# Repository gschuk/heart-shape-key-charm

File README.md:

# Heart-shape-key-charm
This project features a key charm to display simple animations using 7 SMD LEDs. The key charm is meant to be used without a case and includes a hole thoughout the PCB to connect it to a keychain.

<div>
    <div style="display:inline-block; text-align:center;">
        <br>
        <em> Front view </em>
    </div><div style="display:inline-block; text-align:center;">
        <br>
        <em> Back view </em>
    </div>
</div>

## Specification:
Microcontroller: **Attiny 84a** <br>
Powersource: **CR 2032** <br>
LEDs: **Kingsbright red (2mA)** <br>
Power Switch: **Slide Switch (EG1215AA)**<br>

## Documentation:
Software: **firmware/README.md** <br>
Hardware: **hardware/README.md** <br>

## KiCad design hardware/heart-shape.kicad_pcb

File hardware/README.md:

# Hardware
## Components (for one key charm)
- PCB: **FR-4(two layers)** [x1]
- Microcontroller: **Attiny 84a-SS** [x1]
- LEDs: **Kingsbright red (2mA)** [x7] 
- Resistor: **680 ohm (0805)** [x7] 
- Powersource: **CR2032** [x1]
- Coin Cell Holder (CR 2032): **Keystone 1060** [x1]
- Capacitor: **22uF;10V;X5R;(0805)** [x1]
- Slide Switch: **EG1215AA E-Switch** [x1]

## Schematic
<div style="display:inline-block; text-align:center;">
    <br>
    <em> Schematic </em>
</div>

## Driving LEDs
No external LED driver or amplifier was used as the low power LEDs do not require a higher output power than what the Attiny 84a already provides.
### PWM control
The Attiny 84a features 4 PWM pins. In order to control all 7 LEDs, 3 PWM pins are shared by a pair of LEDs: D1 and D4, D2 and D5 as well as D3 and D6. LED D7 does not share a PWM pin and will be driven individually. LEDs that share a PWM pin are located across each other. This allows a circular animation driving 3 neighbouring LEDs with different PWM values at the same time, as every LED and its direct 2 neighbouring LEDs are driven by individual PWM pins.
### Connection to GND or Vcc
Instead of connecting each LED to Vcc or GND statically and controlling the LEDs solely by PWM additional digital pins are used to either turn a single LED on or off. Each LED is connected to one digital pin either driving the output LOW or HIGH. For example: LED D1 and LED D4 share the same PWM signal. If these two LEDs would be statically connected to Vcc or GND they would light up identically. The additional control over the digital pins allows for LED D4 to light up even when LED D1 is turned off.

## Programming Attiny 84a
Pins to program the Attiny 84a are exposed using pads on the backside of the PCB. 
Only use 3 V (or 3.3 V) for powering the key charm! 
| PCB Pad  | Attiny 84a Pin | ISP |
| ------------- | ------------- | ---|
| JF3   | PA4  | SCK   |
| JF4   | PA5  | MISO  |
| JF1   | PA6  | MOSI  |
| JF2   | PB3  | RESET |
| JVcc1 | Vcc  | Vcc   |
| JGND1 | GND  | GND   |

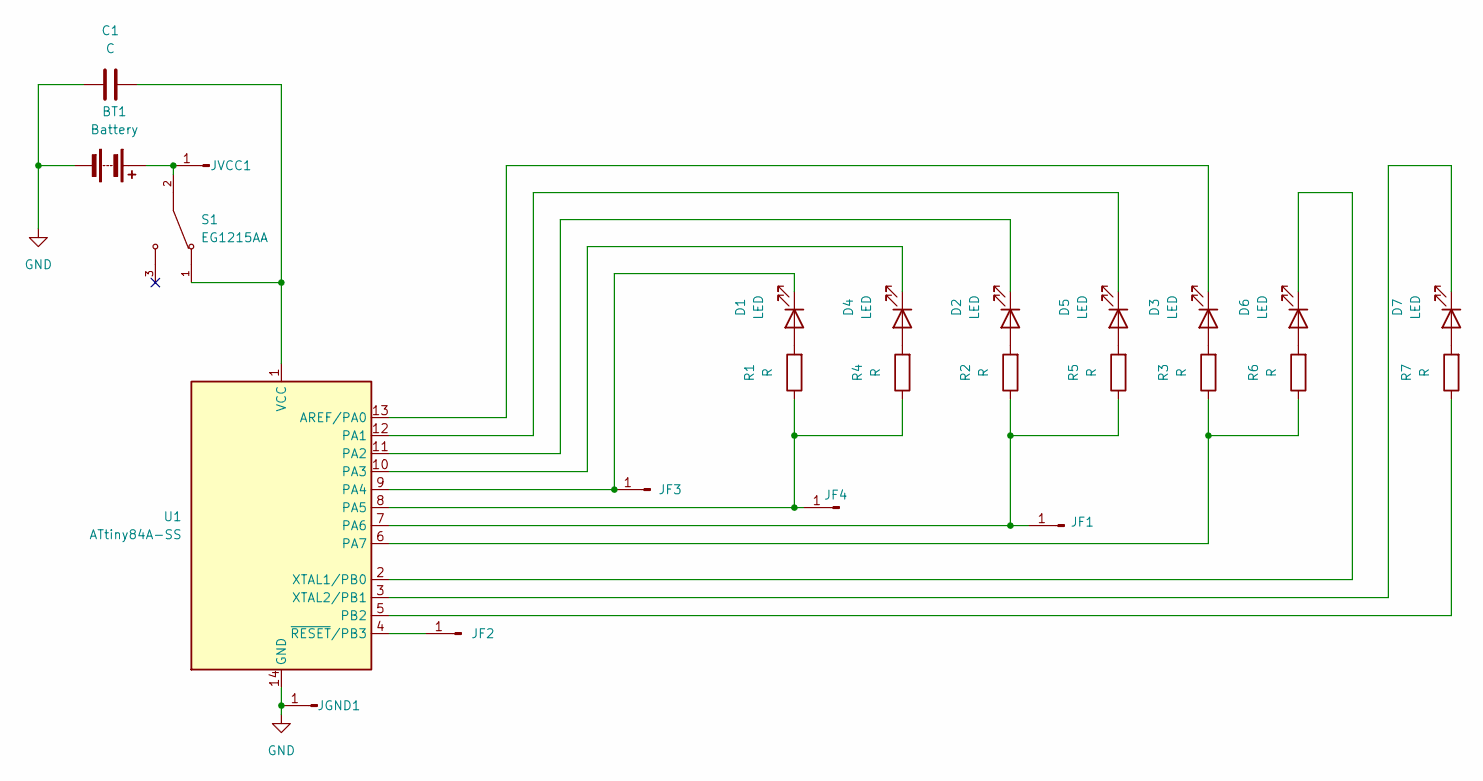
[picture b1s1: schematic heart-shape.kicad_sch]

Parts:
BT1: Battery; BatteryHolder_Keystone_1060_1x2032
C1: C; C_0805_2012Metric_Pad1.18x1.45mm_HandSolder
D1, D2, D3, D4, D5, D6, D7: LED; LED_0805_2012Metric_Pad1.15x1.40mm_HandSolder
JF1, JF2, JF4: Conn_01x01_Pin; TestPoint_Pad_D1.5mm
JF3: TestPoint_Pad_D1.5mm
JGND1: Conn_01x01_Pin; TestPoint_Pad_D1.5mm
JVCC1: Conn_01x01_Pin; TestPoint_Pad_D1.5mm
R1, R2, R3, R4, R5, R6, R7: R; R_0805_2012Metric_Pad1.20x1.40mm_HandSolder
S1: EG1215AA; SW_EG1215AA; PARTREV A
U1: ATtiny84A-SS; SOIC-14_3.9x8.7mm_P1.27mm

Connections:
GND: BT1.2 (-), C1.1, JGND1.1, U1.14 (GND)
unnamed: BT1.1 (+), JVCC1.1, S1.2
unnamed: D1.2 (A), R1.2
unnamed: D1.1 (K), JF3.1, U1.9 (PA4)
unnamed: D2.2 (A), R2.2
unnamed: D2.1 (K), U1.11 (PA2)
unnamed: D3.2 (A), R3.2
unnamed: D3.1 (K), U1.13 (AREF/PA0)
unnamed: D4.2 (A), R4.2
unnamed: D4.1 (K), U1.10 (PA3)
unnamed: D5.2 (A), R5.2
unnamed: D5.1 (K), U1.12 (PA1)
unnamed: D6.2 (A), R6.2
unnamed: D6.1 (K), U1.2 (XTAL1/PB0)
unnamed: D7.2 (A), R7.2
unnamed: D7.1 (K), U1.3 (XTAL2/PB1)
unnamed: JF1.1, R2.1, R5.1, U1.7 (PA6)
unnamed: JF2.1, U1.4 (~RESET/PB3)
unnamed: JF4.1, R1.1, R4.1, U1.8 (PA5)
unnamed: R3.1, R6.1, U1.6 (PA7)
unnamed: R7.1, U1.5 (PB2)
unnamed: C1.2, S1.1, U1.1 (VCC)

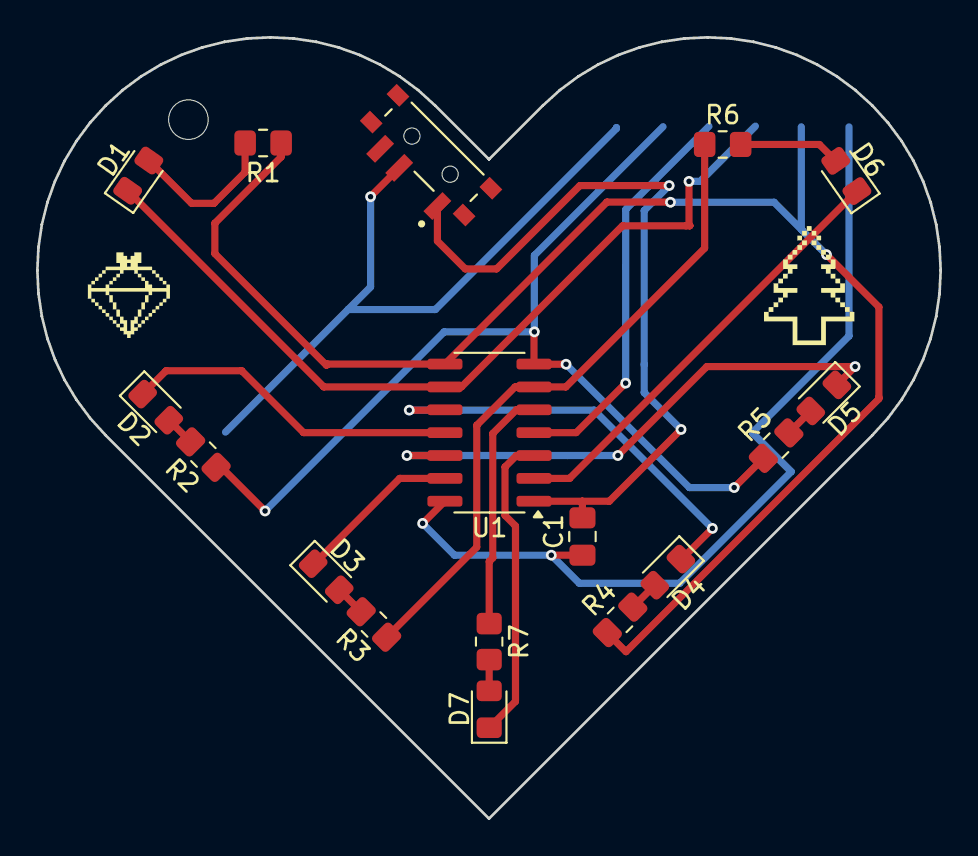
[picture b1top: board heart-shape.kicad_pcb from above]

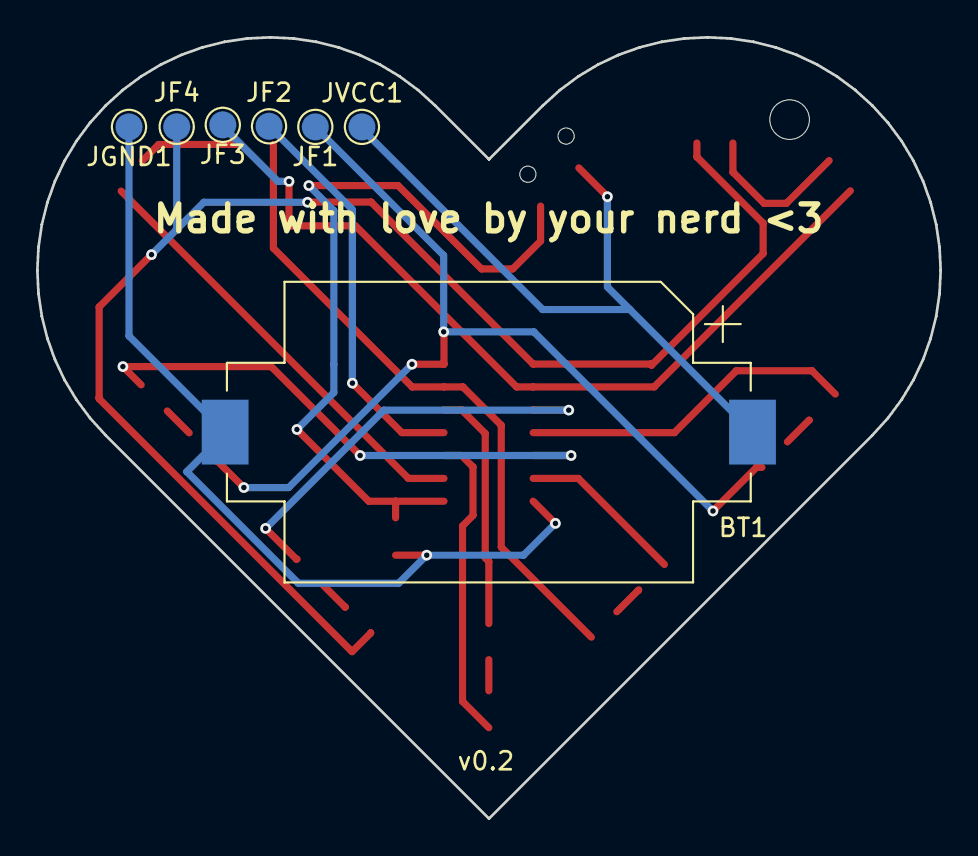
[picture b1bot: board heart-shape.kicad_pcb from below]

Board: 2 copper layers, 50.2 x 43.4 mm, 24 parts (7 on the bottom side), 22 nets.

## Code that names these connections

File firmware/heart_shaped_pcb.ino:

// Correct ATtiny84A pin aliases for ATtinyCore
#define PA0 0
#define PA1 1
#define PA2 2
#define PA3 3
#define PA4 4
#define PA5 5   //PWM
#define PA6 6   //PWM
#define PA7 7   //PWM
#define PB2 8   //PWM
#define PB1 9
#define PB0 10
#define PB3 11

void setup() {
  // put your setup code here, to run once:
  pinMode(PA0, OUTPUT);
  pinMode(PA1, OUTPUT);
  pinMode(PA2, OUTPUT);
  pinMode(PA3, OUTPUT);
  pinMode(PA4, OUTPUT);
  pinMode(PA5, OUTPUT);
  pinMode(PA6, OUTPUT);
  pinMode(PA7, OUTPUT);
  pinMode(PB0, OUTPUT);
  pinMode(PB1, OUTPUT);
  pinMode(PB2, OUTPUT);
  pinMode(PB3, OUTPUT);

  digitalWrite(PA0, LOW);
  digitalWrite(PA1, LOW);
  digitalWrite(PA2, LOW);
  digitalWrite(PA3, LOW);
  digitalWrite(PA4, LOW);
  digitalWrite(PA5, LOW);
  digitalWrite(PA6, LOW);
  digitalWrite(PA7, LOW);

  digitalWrite(PB0, LOW);
  digitalWrite(PB1, LOW);
  digitalWrite(PB2, LOW);
  digitalWrite(PB3, LOW);

  digitalWrite(PA5, HIGH); // PWM: 0 = off, 255 = full on
  digitalWrite(PA6, HIGH); // PWM: 0 = off, 255 = full on
  digitalWrite(PA7, HIGH); // PWM: 0 = off, 255 = full on
  digitalWrite(PB2, HIGH);
  digitalWrite(PB2, HIGH); // PWM: 0 = off, 255 = full on
  delay(1000);
}

void std_blink(unsigned int times = 1, unsigned int delay_twice = 500){
  digitalWrite(PA0, LOW);
  digitalWrite(PA1, LOW);
  digitalWrite(PA2, LOW);
  digitalWrite(PA3, LOW);
  digitalWrite(PA4, LOW);
  digitalWrite(PA5, LOW);
  digitalWrite(PA6, LOW);
  digitalWrite(PA7, LOW);

  digitalWrite(PB0, LOW);
  digitalWrite(PB1, LOW);
  digitalWrite(PB2, LOW);
  digitalWrite(PB3, LOW);

  for (int i = 0; i < times; i++){
    digitalWrite(PA5, HIGH); // PWM: 0 = off, 255 = full on
    digitalWrite(PA6, HIGH); // PWM: 0 = off, 255 = full on
    digitalWrite(PA7, HIGH); // PWM: 0 = off, 255 = full on
    digitalWrite(PB2, HIGH);
    digitalWrite(PB2, HIGH); // PWM: 0 = off, 255 = full on
    delay(delay_twice);
    digitalWrite(PA5, LOW); // PWM: 0 = off, 255 = full on
    digitalWrite(PA6, LOW); // PWM: 0 = off, 255 = full on
    digitalWrite(PA7, LOW); // PWM: 0 = off, 255 = full on
    digitalWrite(PB2, LOW);
    digitalWrite(PB2, LOW); // PWM: 0 = off, 255 = full on
    delay(delay_twice);
  }

}

void fade_in(unsigned int delay_each_step = 10){
  digitalWrite(PA0, LOW);
  digitalWrite(PA1, LOW);
  digitalWrite(PA2, LOW);
  digitalWrite(PA3, LOW);
  digitalWrite(PA4, LOW);
  digitalWrite(PB0, LOW);
  digitalWrite(PB1, LOW);
  digitalWrite(PB3, LOW);
  for (int value = 0; value <= 255; value++) {
    analogWrite(PA5, value); // PWM: 0 = off, 255 = full on
    analogWrite(PA6, value); // PWM: 0 = off, 255 = full on
    analogWrite(PA7, value); // PWM: 0 = off, 255 = full on
    analogWrite(PB2, value); // PWM: 0 = off, 255 = full on
    delay(delay_each_step);
  }
}

void fade_out(unsigned int delay_each_step = 10){
  digitalWrite(PA0, LOW);
  digitalWrite(PA1, LOW);
  digitalWrite(PA2, LOW);
  digitalWrite(PA3, LOW);
  digitalWrite(PA4, LOW);
  digitalWrite(PB0, LOW);
  digitalWrite(PB1, LOW);
  digitalWrite(PB3, LOW);
  for (int value = 255; value >= 0; value--) {
    analogWrite(PA5, value); // PWM: 0 = off, 255 = full on
    analogWrite(PA6, value); // PWM: 0 = off, 255 = full on
    analogWrite(PA7, value); // PWM: 0 = off, 255 = full on
    analogWrite(PB2, value); // PWM: 0 = off, 255 = full on
    delay(delay_each_step);
  }
}

void heartbeat(unsigned int times, int pwm_val){
    analogWrite(PA5, pwm_val); // PWM: 0 = off, 255 = full on
    analogWrite(PA6, pwm_val); // PWM: 0 = off, 255 = full on
    analogWrite(PA7, pwm_val); // PWM: 0 = off, 255 = full on
    analogWrite(PB2, pwm_val); // PWM: 0 = off, 255 = full on
  for(int i = 0; i < times; i++){
        digitalWrite(PA0, LOW);
        digitalWrite(PA1, LOW);
        digitalWrite(PA2, LOW);
        digitalWrite(PA3, LOW);
        digitalWrite(PA4, LOW);
        digitalWrite(PB0, LOW);
        digitalWrite(PB1, LOW);
        digitalWrite(PB3, LOW);
        delay(150);

        digitalWrite(PA0, HIGH);
        digitalWrite(PA1, HIGH);
        digitalWrite(PA2, HIGH);
        digitalWrite(PA3, HIGH);
        digitalWrite(PA4, HIGH);
        digitalWrite(PB0, HIGH);
        digitalWrite(PB1, HIGH);
        digitalWrite(PB3, HIGH);
        delay(150);
        delay(700);

        digitalWrite(PA0, LOW);
        digitalWrite(PA1, LOW);
        digitalWrite(PA2, LOW);
        digitalWrite(PA3, LOW);
        digitalWrite(PA4, LOW);
        digitalWrite(PB0, LOW);
        digitalWrite(PB1, LOW);
        digitalWrite(PB3, LOW);
        delay(150);

        digitalWrite(PA0, HIGH);
        digitalWrite(PA1, HIGH);
        digitalWrite(PA2, HIGH);
        digitalWrite(PA3, HIGH);
        digitalWrite(PA4, HIGH);
        digitalWrite(PB0, HIGH);
        digitalWrite(PB1, HIGH);
        digitalWrite(PB3, HIGH);
        delay(150);
  }
}

void ring_dimming(unsigned int delay_each_step = 10){
  int steps_per_phase = 255/3;
  digitalWrite(PA0, LOW);
  digitalWrite(PA1, HIGH);
  digitalWrite(PA2, LOW);
  digitalWrite(PA3, HIGH);
  digitalWrite(PA4, LOW);
  digitalWrite(PB0, HIGH);
  digitalWrite(PB1, HIGH);
  digitalWrite(PB3, HIGH);
  int phase1 = 0, phase2 = 255, phase3 = 255;


  phase1 = 0;
  phase2 = 255;
  phase3 = 255;
  for (int i = 0; i < 255; i++){
    analogWrite(PA7, phase1++); //phase1: rising
    analogWrite(PA6, phase2); //phase2: holding
    analogWrite(PA5, phase3--); //phase3: falling
    delay(delay_each_step);
  }

  phase1 = 0;
  phase2 = 255;
  phase3 = 255;
  digitalWrite(PB1, LOW);
  digitalWrite(PA4, HIGH);
  for (int i = 0; i < 255; i++){
    analogWrite(PB2, phase1++); //phase1: rising
    analogWrite(PA7, phase2); //phase2: holding
    analogWrite(PA6, phase3--); //phase3: falling
    delay(delay_each_step);
  }
  phase1 = 0;
  phase2 = 255;
  phase3 = 255;
  digitalWrite(PA3, LOW);
  digitalWrite(PA2, HIGH);
  for (int i = 0; i < 255; i++){
    analogWrite(PA5, phase1++); //phase1: rising
    analogWrite(PB2, phase2); //phase2: holding
    analogWrite(PA7, phase3--); //phase3: falling
    delay(delay_each_step);
  }
  phase1 = 0;
  phase2 = 255;
  phase3 = 255;
  digitalWrite(PA1, LOW);
  digitalWrite(PA0, HIGH);
  for (int i = 0; i < 255; i++){
    analogWrite(PA6, phase1++); //phase1: rising
    analogWrite(PA5, phase2); //phase2: holding
    analogWrite(PB2, phase3--); //phase3: falling
    delay(delay_each_step);
  }

  phase1 = 0;
  phase2 = 255;
  phase3 = 255;
  digitalWrite(PB0, LOW);
  digitalWrite(PB1, HIGH);
  for (int i = 0; i < 255; i++){
    analogWrite(PA7, phase1++); //phase1: rising
    analogWrite(PA6, phase2); //phase2: holding
    analogWrite(PA5, phase3--); //phase3: falling
    delay(delay_each_step);
  }

  phase1 = 0;
  phase2 = 255;
  phase3 = 255;
  digitalWrite(PA4, LOW);
  digitalWrite(PA3, HIGH);
  for (int i = 0; i < 255; i++){
    analogWrite(PA5, phase1++); //phase1: rising
    analogWrite(PA7, phase2); //phase2: holding
    analogWrite(PA6, phase3--); //phase3: falling
    delay(delay_each_step);
  }

  phase1 = 0;
  phase2 = 255;
  phase3 = 255;
  digitalWrite(PA2, LOW);
  digitalWrite(PA1, HIGH);
  for (int i = 0; i < 255; i++){
    analogWrite(PA6, phase1++); //phase1: rising
    analogWrite(PA5, phase2); //phase2: holding
    analogWrite(PA7, phase3--); //phase3: falling
    delay(delay_each_step);
  }
}

void loop() {
  std_blink(5);
  ring_dimming(1);
  ring_dimming(1);
  ring_dimming(1);
  ring_dimming(1);
  ring_dimming(1);
  ring_dimming(1);
  ring_dimming(5);
  ring_dimming(5);
  ring_dimming(5);
  ring_dimming(5);
  ring_dimming(5);
  ring_dimming(5);
  heartbeat(20, 50);
  fade_in(5);
  fade_out(5);
  fade_in();
  fade_out();
  heartbeat(20, 50);
  fade_in(1);
  fade_out(1);
  fade_in(1);
  fade_out(1);
  ring_dimming(10);
  ring_dimming(10);
  ring_dimming(10);
  heartbeat(20, 50);
}

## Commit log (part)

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2026-04-29 hardware: init and current state
    - Created git
    - Updated Edgecut SVG to DXF
    - Edgecut now gets rendered in 3D viewer
    - Fixed Minor error with silkscreen
2026-05-04 Readme / Hardware: Created general Readme / Small fixes on the silkscreen of PCB - First Version of README.md - Moved and corrected silkscreen for label of LEDs
2026-05-04 Readme: Added figures folder - Created figures folder - Added frontside of PCB 3D viewer - Added backside of PCB 3D viewer - Added figures to README.md
2026-05-05 Readme: Added Schematic Figure and created hardware Readme - Schematic Figure - Created Hardware README.md - Driving LED Section - Components Section
2026-05-07 Readme/Hardware: Updated hardware/README.md / Added JFVcc1 JFGND1 - Added Section Programming Attiny 84a - Updated Schematic in README - Added JFVcc1 and JFGND1 in Schematic and PCB layout
2026-05-07 Firmware / Readme: Added example Firmware / Added Readme for example Firmware - heart_shaped_pcb.ino - Added section Ring Dimming - Flashing
2026-06-13 Updated PCB Design: -Removed ring on silkmask from battery case
    Updated firmare/Readme.md:
    - updated explenation of Ring Dimming
